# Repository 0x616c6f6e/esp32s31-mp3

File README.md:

# ESP32-S31 MP3 / Q2 风格播放器

当前工程：

- **[V2 裸芯片主板 PCB](hardware-q2-v2/README.md)**：打开 `hardware-q2-v2/q2-v2.kicad_pro`。ESP32-S31NRV16、正面 AM213 BTB、46 × 76 mm 六层板，0201 阻容已改为 0402。当前仅保留电源布线与铺铜，信号待手动布线；几何 DRC、电源未连接及原理图一致性均为 0，174 项信号飞线为有意保留，不能直接投产。[双面预览](hardware-q2-v2/output/pcb-overview.png)。
- [V2 布局及管脚规划依据](hardware-q2-v2-plan/README.md)：保留方案来源；实际已布线管脚以 [V2 当前引脚表](hardware-q2-v2/pin-assignment.md) 为准。

**当前开发外壳为 L 版：适配新的 2.13 英寸 AM213 AMOLED。** 已修改屏幕总成、面壳开孔和固定台，整机仍为50×81.5×15.1 mm。新屏24针BTB不能直接连接已生产主板的21针FPC2，已完成独立双层FPC转接板的3.3 V参考电路和布线；ERC/DRC及原理图一致性检查通过。L版已有完整转接板装配检查副本，仍待FPC工艺审核、实物插合和点亮测试。

- **[最新外壳 L：2.13英寸屏幕适配](mechanical/enclosure-final-l/README.md)**：`Q2_L_AM213_Adapter_Study.FCStd`，直接使用新屏自带触摸盖板，预留17×22 mm转接板空间。[转接板接线规划](hardware-display-adapter/README.md)。

- **[历史外壳 K：旧2.09英寸屏幕](mechanical/enclosure-final-k/README.md)**：`Q2_K_Assembly_Access.FCStd`。已修复J版装入路径与薄壁，但不适用新AM213屏幕；保留作历史参考。

- **[历史外壳 J：后盖胶粘铜螺母版](mechanical/enclosure-final-j/README.md)**：打样复查暂缓，见 [J 版问题记录](mechanical/enclosure-final-j/PREFLIGHT-REVIEW.md)。已由 K 版取代。

- **[历史外壳 I：装配优化版](mechanical/enclosure-final-i/README.md)**：`Q2_I_Serviceable_Assembly.FCStd`。小板采用三颗带限长垫片的螺钉＋侧边限位台，避开 FFC；加厚按键止脱边、增加排线槽与绝缘护边。修正 G/H 版复合实体干涉漏报，使用 I 版完整四件打印包。

- **[历史外壳 H：小板固定加强版](mechanical/enclosure-final-h/README.md)**：`Q2_H_Reinforced_Assembly.FCStd`。加粗四个小板螺柱、加宽根部并增加侧壁加强筋，小板螺钉改为头下长 2 mm 的 M1.6；外形及两板位置沿用 G 版。使用 H 版打印包，G 版保留为历史。

- **[历史外壳 G：薄型树脂装机样件](mechanical/enclosure-final-g/README.md)**：`Q2_G_Thin_Assembly.FCStd`，适配最终主板与 CH32V006 小板，50 × 81.5 × 14.2 mm（含盖板）。CN2/CN3 改为直接焊线装配；修正支柱、马达托座、屏幕排线和按键避让。附四件打印文件。电池成品厚度仍待供方确认，装机约束见说明。

- [最终主板与按键板 FreeCAD 检查](mechanical/final-board-review/README.md)：采用 `hardware-q2/ProPrj_esp32s31-mp4_2026-09-22.kicad_pro` 为最终主板；两板已导入 `Q2_Final_Mainboard_Assembly.FCStd`。四个主板安装孔与原柱对齐，但发现马达/耳机座、C13/屏幕排线干涉，详见检查报告。

- [独立滑环与按键小板 C](hardware-controls/README.md)：打开 `hardware-controls/controls.kicad_pro`；44 × 34 × 0.8 mm，CH32V006F8U6 读取触摸环与四个机械键，通过 I²C 上报，POWER 独立上拉、按下为低；使用 12P / 0.5 mm / 40 mm 异面 FFC。当前整机机械装配见 K 版外壳，需另行完成小板固件及实物触摸标定。
- [已生产的模组版主板](hardware-q2/ProPrj_esp32s31-mp4_2026-09-22.kicad_pro)：当前保存工程为 `ProPrj_esp32s31-mp4_2026-09-22`；原始生产 Gerber 的审查记录见 [打板检查](hardware-q2/gerber-review-20260922/README.md)。
- [H1/H2 端子、马达和电池规划](mechanical/connector-layout/README.md)：当前摆放版使用 JST ACH 两芯/三芯端子，新增 FreeCAD 装配及线束通道检查。
- [历史外壳 F](mechanical/enclosure-q2-f/README.md)：保留早期外观方案；当前装配应参考 L 版。

旧 `hardware/`、`hardware-q2-placement/` 和旧主板导出文件已从当前目录移除，可从 Git 历史查找。根目录的 PDF、嘉立创 `.epro2` / `.epro` 及 Gerber 压缩包是原始资料。

历史摆放版已有主板与外壳适配；用户新布局 `hardware-q2-layout` 已用于最新小板/排线装配，其最终版本的四个主板安装孔已确认与原柱对齐；完整复查以最新报告为准。屏幕 FPC 插接细节、完整器件高度、具体电池型号仍需确认。独立滑环及五键小板见 `hardware-controls/`；两板接口针序已核对，排线插接、小板触摸与摇摆按键仍需实物验证。[排线采购与装配说明](hardware-controls/mechanical/FFC-INTERCONNECT.md)。详细尺寸、检查范围和后续事项见上述工程说明。

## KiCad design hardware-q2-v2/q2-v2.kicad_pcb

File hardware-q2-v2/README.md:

# Q2 V2 裸芯片主板 · 2026-09-24

打开 **q2-v2.kicad_pro**。这是 ESP32-S31NRV16 裸芯片版的独立工程，当前按用户要求改为 **0402 阻容、电源分区铺铜并就近打过孔，信号待手动布线**。不是可打板文件。原生产主板 `hardware-q2` 的 PCB 保持原文件哈希。

此前将 21 个电容、10 个电阻及 L105（实际为 0Ω 电阻）从英制 0201 改为 0402（公制 1005）；L101–L104 的射频/滤波电感不在阻容替换范围内。随后检查发现原嘉立创导入的 0402 与 KiCad 标准焊盘混用，现已统一全部 62 个电阻类封装（含 L105）及 72 个电容封装，原理图、符号库、PCB 和 3D 模型同步使用下面两套项目内标准封装。密集区已调整间距，接口和安装孔位置保持不变。

| 类型 | 项目封装 | 焊盘尺寸 | 两焊盘中心距 |
|---|---|---|---|
| 0402 电阻 | `V2:R_0402_1005Metric` | 0.54 × 0.64 mm，圆角矩形 | 1.02 mm |
| 0402 电容 | `V2:C_0402_1005Metric` | 0.56 × 0.62 mm，圆角矩形 | 0.96 mm |

两者来自 KiCad 10 标准库，阻焊/锡膏使用标准继承设置。原有 0603/0805 电容和 1206 电流采样电阻保留原尺寸；过时的 134 个按位号命名的 0402 封装已移除，避免误用。`0402-standardization.json` 记录原始尺寸、统一后尺寸、位置及检查结果；运行 `scripts/audit_0402.py` 可核对所有实例的焊盘、阻焊/锡膏、模型及原理图关联。

删除了 2,090 段信号走线、155 个信号过孔；另重建主控局部电源引出。保留供电、GND/GBAT、稳压器开关/反馈/自举、电荷泵及马达负载回路。电源使能、温度采样、通信、时钟、射频、音频输出等信号均需后续手动布线。精确网络允许列表和改封装清单见 `power-only-0402.json`。

## 工程内容

- `q2-v2.kicad_pcb`：46 × 76 mm，6 层，名义板厚 1.6 mm；198 个器件，双面装配，普通通孔。
- `q2-v2.kicad_sch`：根页及 19 个功能子页，与 PCB 的器件实例和编号焊盘关联。
- `V2.kicad_sym`、`V2.pretty`、`models3d`：项目局部符号、封装和模型。常规 R/C/L 使用 KiCad 标准模型，需安装 KiCad 10 的 3D 模型库。
- `pin-assignment.md`、`q2_v2_pins.h`：从实际 PCB 生成的管脚表和 GPIO 宏；不是已验证的 BSP。
- `output/drc.json`、`erc.json`、`netlist-consistency.json`、`validation-summary.json`：最终检查记录。
- `output/q2-v2-assembly.step`、`case-fit.json`：主板装配模型及相对 L 版外壳的名义干涉检查。
- `output/front-review.svg/png`、`back-review.svg/png`：布局预览；`output/assembly-front.svg`、`assembly-back.svg` 为装配图。
- `output/power-map.svg/png`：In2/In3 实际填充后的电源铜区，按网络着色，均为顶视坐标；`power-pours.json` 记录铜区面积及电源连通性检查。
- 本地 `output/archive` 和路由会话为未提交的中间候选；Git 保留最终报告、模型与建板基线。`scripts` 中的建板及试布线脚本是过程记录，部分依赖本地路由运行时。**不要重新运行 build_v2、prepare_routing、route_usb_and_export 等初始化脚本覆盖当前成品布线。**

## 实现的电路与布局

主控改为 ESP32-S31NRV16，采用乐鑫官方 WROOM-3 V1.2 参考设计的裸芯片电源、40 MHz 晶振、PSRAM 供电和射频匹配起始网络，外接 W25Q128JVSIQ 16 MB 启动 Flash。天线暂定 U.FL/IPEX 外接柔性天线，尚未选定最终天线及安装位置。

屏幕采用正面 OK-23GF024-04，JDISP1 中心以板框左上原点计 `(30.0, 29.2) mm`，旋转 90°。板框原点对应 KiCad 坐标 `(128.868, 67.647) mm`。主控、存储和射频在上部，音频在左下，充电、USB 和电池接口在下部；新增低速电路主要放在背面。

为保持已完成 CH32 按键板的 POWER 上拉行为，新增常供电 3.3 V、跨断电电源域的信号隔离和关机脉冲电路。FPC1 的 2 脚改由常供电 3.3 V 供电；系统 I²C 使用 GPIO6/7 的 **LP I²C**，不能当成第三个普通 HP I²C 控制器初始化。UART 自动下载采用交叉晶体管电路；GPIO60/61 为启动配置，GPIO0 用于按键检测。

已修正 V1 中 CS43131 的 SCL/SDA 对应关系：物理 1 脚 SCL、39 脚 SDA。USB 屏蔽固定焊盘接地，USB 定位孔按厂家图改为 Ø0.55 mm NPTH。保留原外部接口和安装孔锚点。

| 焊线接口 | 焊盘 | 网络 | 用途 |
|---|---|---|---|
| CN2 | 1 | VBAT | 电池正极 |
| CN2 | 2 | BAT_TS | 电池温度检测，不可当作负极 |
| CN2 | 3 | GBAT | 电池负极，保留电量计采样回路，不要任意短接到其它 GND 点 |
| CN3 | 1 / 2 | MOTOR_OUT_P / MOTOR_OUT_N | 马达两端，均不是直接接地端 |

## 校验结果及边界

当前原生 KiCad 10 检查：**几何 DRC 违规 0 项、原理图一致性 0 项、电源未连接 0 项；信号未连接 174 项，符合本次保留飞线的要求**。原理图电路未改变，既有 ERC 为 0 项；另重新逐项比对 198 个器件、704 个编号焊盘的 XML 网表与 PCB，网络不一致为 0。所有阻容均已无 0201 封装，信号走线/过孔残留为 0。

DRC 使用工程内设置：最小线宽/间距 0.10/0.10 mm，保留少量 Ø0.35/0.15 mm 通孔，常规过孔 Ø0.45/0.20 mm；两层连续 GND 加外层铺地及就近地过孔。DRC 和铜区连通性检查不能替代电流/温升验证。

### 电源铺铜与过孔

本次不移动器件或更改原理图网络。In2.Cu（PWR）以 VCC_3V3 为主，In3.Cu（工程名称 SINGAL）放置其余局部电源铜区，必要的跨区连接借用少量 In2 区域。包括 GBAT 在内共 12 个供电/回流分区，彼此保持网络隔离；In1/In4 继续作为整面公共 GND。后续布信号需避开这些电源铜区，或重新填铜并复查电源连通性。

删除直流供电网络的内层分配走线，改为实际连通的铺铜；焊盘附近采用 Ø0.45/0.20 mm、双面盖油的过孔连接内层。普通电源孔避开 SMD 焊盘，保留必要的短表层引出，单段最长 2.0 mm；充电器和降压的大电流节点补充并联过孔。开关节点、反馈、自举、电荷泵以及马达负载回路仍保留必要短线，不能直接视为直流电源平面。主控原有 GND 散热焊盘通孔保留。

`scripts/audit_power_pours.py` 核对电源及地无未连接、直流内层分配线为零、信号铜残留为零，并输出实际填充铜区图。`build_power_pours.py` 和 `bridge_power_pours.py` 是生成过程脚本，依赖本地未提交的 `output/power-pour-spines.kicad_pcb`；不要作为日常更新命令重复执行。后续直接在 KiCad 编辑当前 PCB 并按 B 重新填铜。旧的 `output/power-width-*.json`、`retained-routing.json` 为改铺铜前的历史检查，本版以 `power-pours.json` 和 `validation-summary.json` 为准。

`drc.json` 明列 5 类未启用检查，包括缺少 courtyard、线端未居中过孔等，不能把 0 项理解为完整 DFM 认证。导入封装没有统一的装配 courtyard；已用名义 3D 模型补充器件碰撞检查，但没有验证供应商公差或装配工具空间。

FreeCAD 检查未发现器件模型之间的实体重叠，亦未发现主板组件与所选 L 版外壳、后盖、电池及马达占位的硬碰撞。仅 FPC1 与按键排线插入包络重叠约 1.071 mm³，属于预期插接区域。螺钉孔、测试点、CN2/CN3 焊线焊盘没有实体器件模型；新增晶振和主控模型为名义外形。该结果不等同于屏幕尾排线可插入、插拔路径和尺寸公差已验证。

## 打板前尚待完成的签核

1. **完成所有信号布线。** 包括电源使能、温度采样、USB、Flash、屏幕、音频、射频和晶振。USB 旧版线长结果已失效；`output/usb-routing.json` 是改版前的历史记录，不代表当前 PCB。下单前选定厂家叠层，计算线宽、间距、参考面并复核全链路差分耦合与偏斜；目前没有受控阻抗签核。
2. **射频与晶振。** 匹配值来自官方模块参考，但参考模块叠层不同，不能直接等同于本板的 50 Ω。本次匹配/负载电容及 0Ω 链路放大为 0402，寄生参数变化，原值仅保留为调试起点；需重布短线并实测匹配和晶振。40 MHz 晶振需匹配负载、精度及封装，不能只按频率采购。
3. **AM213 屏幕。** 按此前用户决定继续使用 3.3 V；项目内已保存的 [OSPTEK 官方参考原理图](../hardware-display-adapter/reference/osptek-official/PCB-2.13&1.96AMOLED-qspi转接板.pdf) 将 AM213 的 11/12/15/16 脚接到 VCC3V3，因此有原厂参考电路依据。该接法与早期规格书 PMIC 最低 3.4 V 的文字仍有差异，需实测启动、最大亮度、电源余量和温度边界，不能当作所有屏幕批次的保证。BTB 朝向、尾排线实际折弯与够长需用实物确认，不能仅靠 nominal STEP 认定可插接。
4. **供电和装配工艺。** 裸芯片 EP 内含 25 个散热通孔，需向板厂确认树脂填孔、电镀盖孔/平整焊盘工艺，避免焊料流失；0.15 mm 小孔、细线距及双面装配须与所选订单工艺一致。验证充电/峰值电流、主电源掉电、AON 反灌隔离及关机脉冲时序；尚未做上电、固件、信号完整性、热或 EMC 测试。

因此本目录交付的是**供手动完成信号布线的 PCB 工程**，没有导出标为可生产的 Gerber 包。

## 音频接地与后续布线

本板建议保留连续的公共 GND 平面，通过器件分区和回流路径隔离噪声，不另建孤立 AGND 铜岛或在 I²S 回流下开地缝。充电、降压与马达的大电流回路应局部闭合并远离 DAC/耳机回路；音频电源的滤波与去耦独立考虑。GBAT 是电量计采样回路，不是音频地，不可直接并到其它地焊盘。

**HPREFA/HPREFB 是例外的参考回路要求，不等于整块音频分地。** CS43131 手册第 8.3 节要求 U2 的 13、17 脚分别独立走线到耳机座参考地，再在耳机座地处通过过孔接系统地。目前这两脚仍归属公共 GND，现有铺铜会直接接入，尚未实现 Kelvin 回路。手动布线时应使用独立参考地网络与耳机座处的 net-tie（或局部禁布铜并严格控制公共网拓扑）实现，不能将当前公共地填充视为该要求已满足。GNDA/GNDD/GNDCP 和散热焊盘则继续采用低阻抗接地。依据：[CS43131 数据手册第 8.1–8.4 节](https://statics.cirrus.com/pubs/proDatasheet/CS43131_DS1155F2.pdf#page=140)。

## 参考依据

- [乐鑫 ESP32-S31 硬件设计指南](https://docs.espressif.com/projects/esp-hardware-design-guidelines/en/latest/esp32s31/schematic-checklist.html)，以及项目内 `esp32-s31_datasheet_en.pdf` v0.5；官方模块参考工程保存在 `reference/s31-module`。
- [CS43131 官方手册](https://statics.cirrus.com/pubs/proDatasheet/CS43131_DS1155F2.pdf)。
- [嘉立创 PCB 制程能力](https://jlcpcb.com/capabilities/pcb-capabilities)与[受控阻抗叠层](https://jlcpcb.com/impedance)。生产叠层和工艺应以实际订单确认为准。

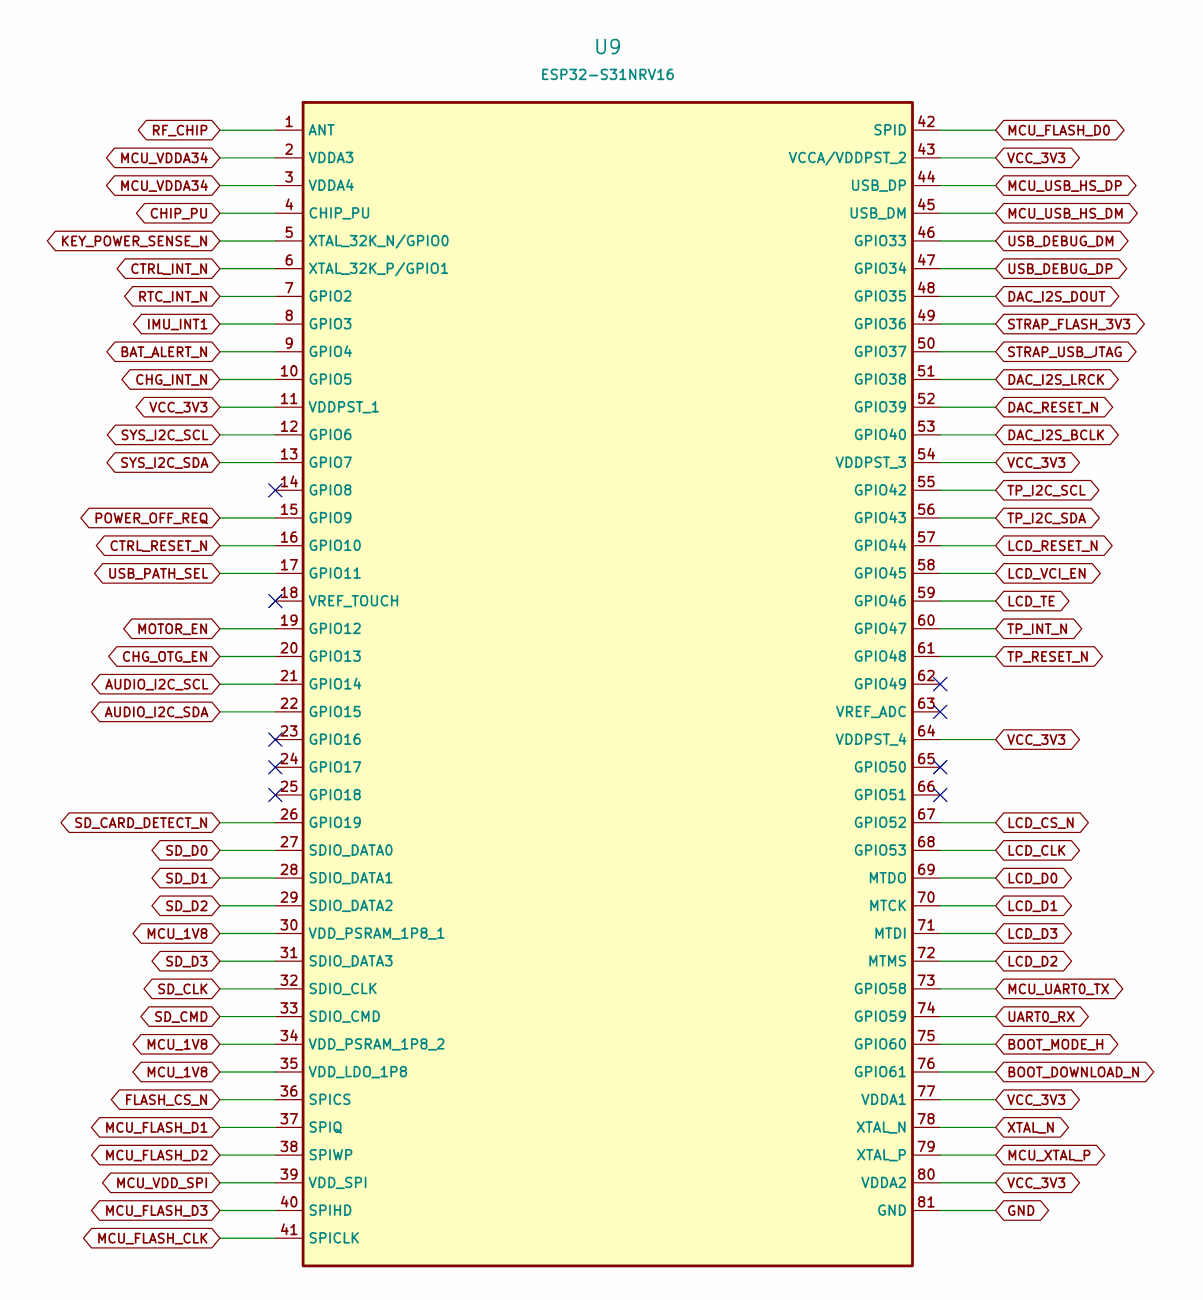
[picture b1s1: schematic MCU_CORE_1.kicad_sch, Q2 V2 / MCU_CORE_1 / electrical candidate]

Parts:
U9: ESP32-S31NRV16; FP_U9

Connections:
AUDIO_I2C_SCL: U9.21 (GPIO14); also elsewhere on the board
AUDIO_I2C_SDA: U9.22 (GPIO15); also elsewhere on the board
BAT_ALERT_N: U9.9 (GPIO4); also elsewhere on the board
BOOT_DOWNLOAD_N: U9.76 (GPIO61); also elsewhere on the board
BOOT_MODE_H: U9.75 (GPIO60); also elsewhere on the board
CHG_INT_N: U9.10 (GPIO5); also elsewhere on the board
CHG_OTG_EN: U9.20 (GPIO13); also elsewhere on the board
CHIP_PU: U9.4 (CHIP_PU); also elsewhere on the board
CTRL_INT_N: U9.6 (XTAL_32K_P/GPIO1); also elsewhere on the board
CTRL_RESET_N: U9.16 (GPIO10); also elsewhere on the board
DAC_I2S_BCLK: U9.53 (GPIO40); also elsewhere on the board
DAC_I2S_DOUT: U9.48 (GPIO35); also elsewhere on the board
DAC_I2S_LRCK: U9.51 (GPIO38); also elsewhere on the board
DAC_RESET_N: U9.52 (GPIO39); also elsewhere on the board
FLASH_CS_N: U9.36 (SPICS); also elsewhere on the board
GND: U9.81 (GND); also elsewhere on the board
IMU_INT1: U9.8 (GPIO3); also elsewhere on the board
KEY_POWER_SENSE_N: U9.5 (XTAL_32K_N/GPIO0); also elsewhere on the board
LCD_CLK: U9.68 (GPIO53); also elsewhere on the board
LCD_CS_N: U9.67 (GPIO52); also elsewhere on the board
LCD_D0: U9.69 (MTDO); also elsewhere on the board
LCD_D1: U9.70 (MTCK); also elsewhere on the board
LCD_D2: U9.72 (MTMS); also elsewhere on the board
LCD_D3: U9.71 (MTDI); also elsewhere on the board
LCD_RESET_N: U9.57 (GPIO44); also elsewhere on the board
LCD_TE: U9.59 (GPIO46); also elsewhere on the board
LCD_VCI_EN: U9.58 (GPIO45); also elsewhere on the board
MCU_1V8: U9.30 (VDD_PSRAM_1P8_1), U9.34 (VDD_PSRAM_1P8_2), U9.35 (VDD_LDO_1P8); also elsewhere on the board
MCU_FLASH_CLK: U9.41 (SPICLK); also elsewhere on the board
MCU_FLASH_D0: U9.42 (SPID); also elsewhere on the board
MCU_FLASH_D1: U9.37 (SPIQ); also elsewhere on the board
MCU_FLASH_D2: U9.38 (SPIWP); also elsewhere on the board
MCU_FLASH_D3: U9.40 (SPIHD); also elsewhere on the board
MCU_UART0_TX: U9.73 (GPIO58); also elsewhere on the board
MCU_USB_HS_DM: U9.45 (USB_DM); also elsewhere on the board
MCU_USB_HS_DP: U9.44 (USB_DP); also elsewhere on the board
MCU_VDDA34: U9.2 (VDDA3), U9.3 (VDDA4); also elsewhere on the board
MCU_VDD_SPI: U9.39 (VDD_SPI); also elsewhere on the board
MCU_XTAL_P: U9.79 (XTAL_P); also elsewhere on the board
MOTOR_EN: U9.19 (GPIO12); also elsewhere on the board
POWER_OFF_REQ: U9.15 (GPIO9); also elsewhere on the board
RF_CHIP: U9.1 (ANT); also elsewhere on the board
RTC_INT_N: U9.7 (GPIO2); also elsewhere on the board
SD_CARD_DETECT_N: U9.26 (GPIO19); also elsewhere on the board
SD_CLK: U9.32 (SDIO_CLK); also elsewhere on the board
SD_CMD: U9.33 (SDIO_CMD); also elsewhere on the board
SD_D0: U9.27 (SDIO_DATA0); also elsewhere on the board
SD_D1: U9.28 (SDIO_DATA1); also elsewhere on the board
SD_D2: U9.29 (SDIO_DATA2); also elsewhere on the board
SD_D3: U9.31 (SDIO_DATA3); also elsewhere on the board
STRAP_FLASH_3V3: U9.49 (GPIO36); also elsewhere on the board
STRAP_USB_JTAG: U9.50 (GPIO37); also elsewhere on the board
SYS_I2C_SCL: U9.12 (GPIO6); also elsewhere on the board
SYS_I2C_SDA: U9.13 (GPIO7); also elsewhere on the board
TP_I2C_SCL: U9.55 (GPIO42); also elsewhere on the board
TP_I2C_SDA: U9.56 (GPIO43); also elsewhere on the board
TP_INT_N: U9.60 (GPIO47); also elsewhere on the board
TP_RESET_N: U9.61 (GPIO48); also elsewhere on the board
UART0_RX: U9.74 (GPIO59); also elsewhere on the board
USB_DEBUG_DM: U9.46 (GPIO33); also elsewhere on the board
USB_DEBUG_DP: U9.47 (GPIO34); also elsewhere on the board
USB_PATH_SEL: U9.17 (GPIO11); also elsewhere on the board
VCC_3V3: U9.11 (VDDPST_1), U9.43 (VCCA/VDDPST_2), U9.54 (VDDPST_3), U9.64 (VDDPST_4), U9.77 (VDDA1), U9.80 (VDDA2); also elsewhere on the board
XTAL_N: U9.78 (XTAL_N); also elsewhere on the board

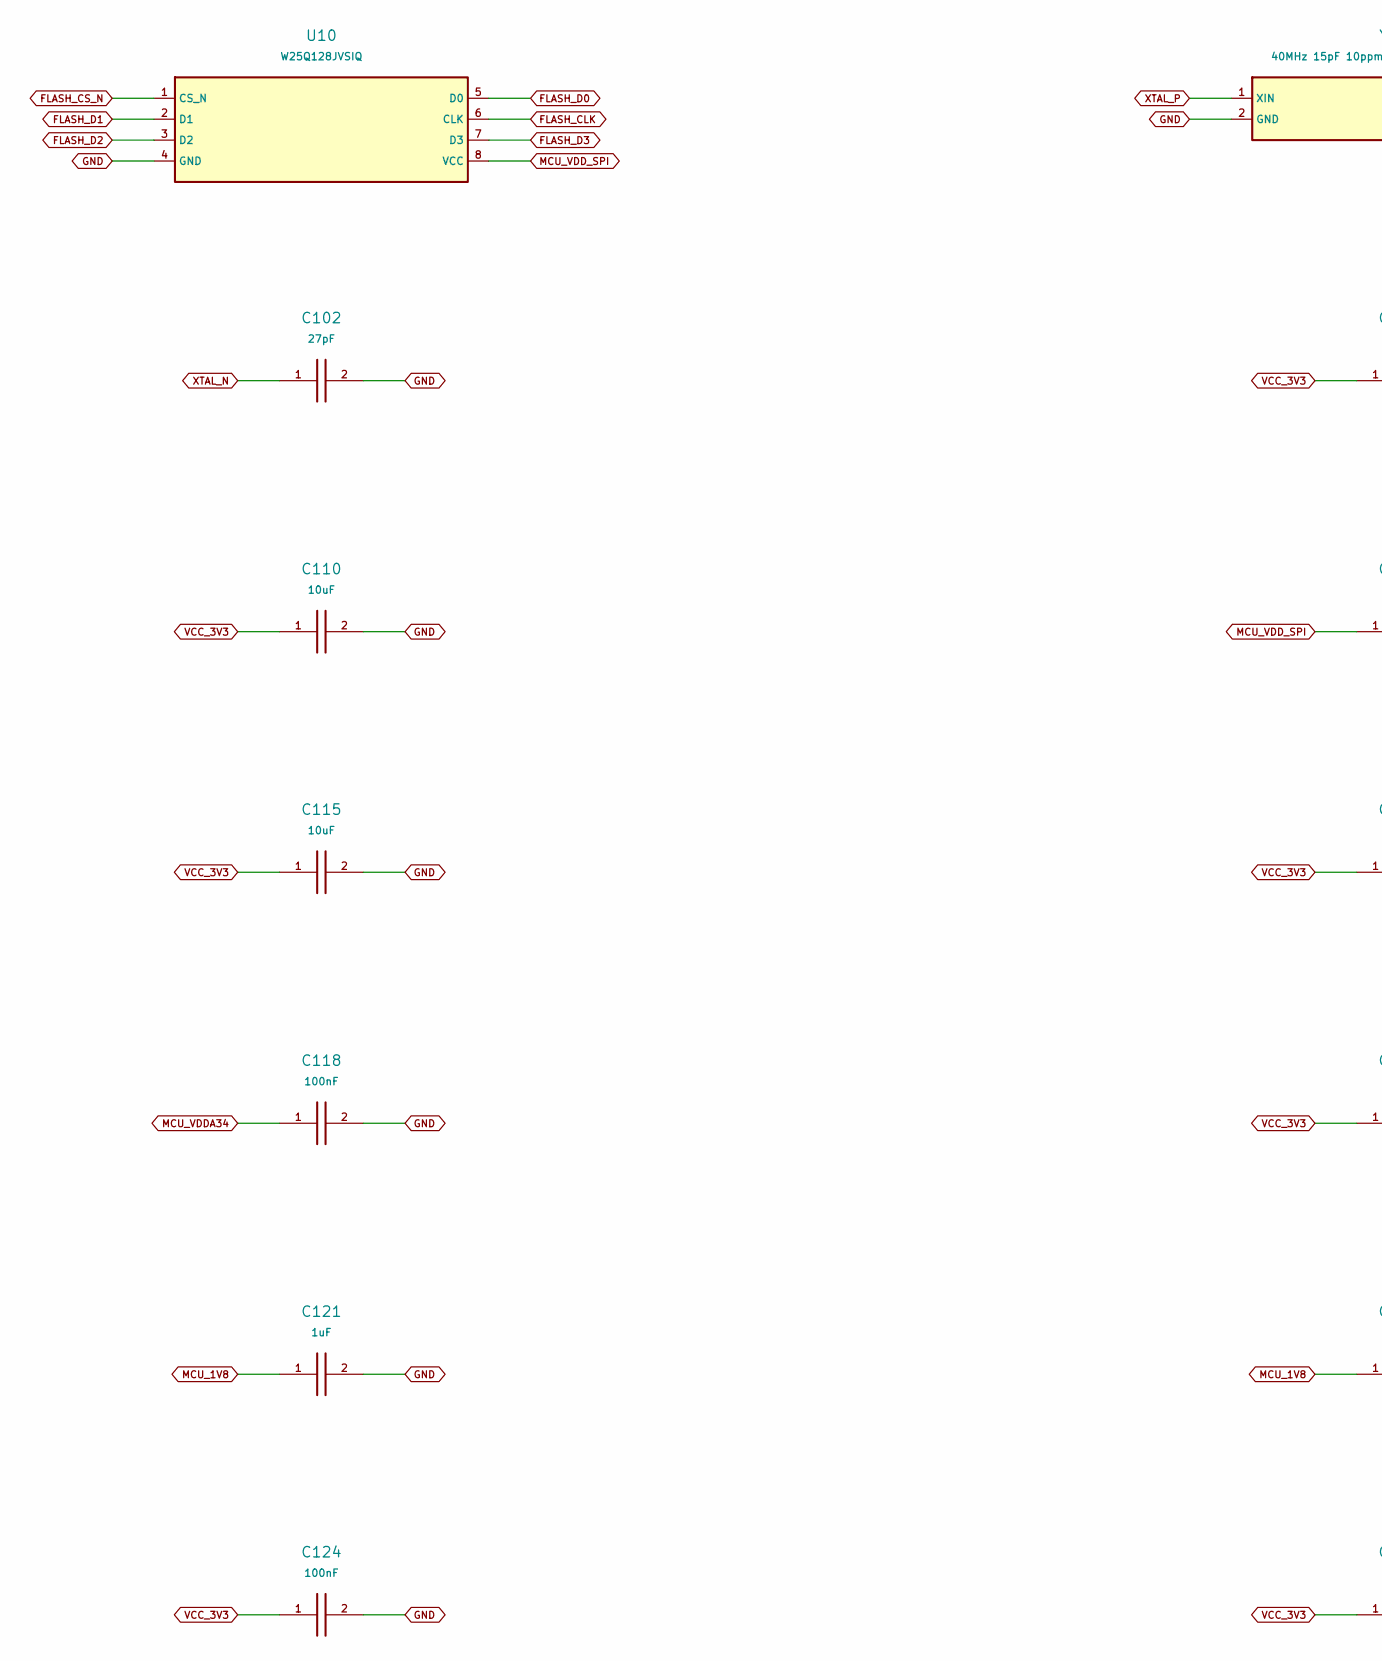
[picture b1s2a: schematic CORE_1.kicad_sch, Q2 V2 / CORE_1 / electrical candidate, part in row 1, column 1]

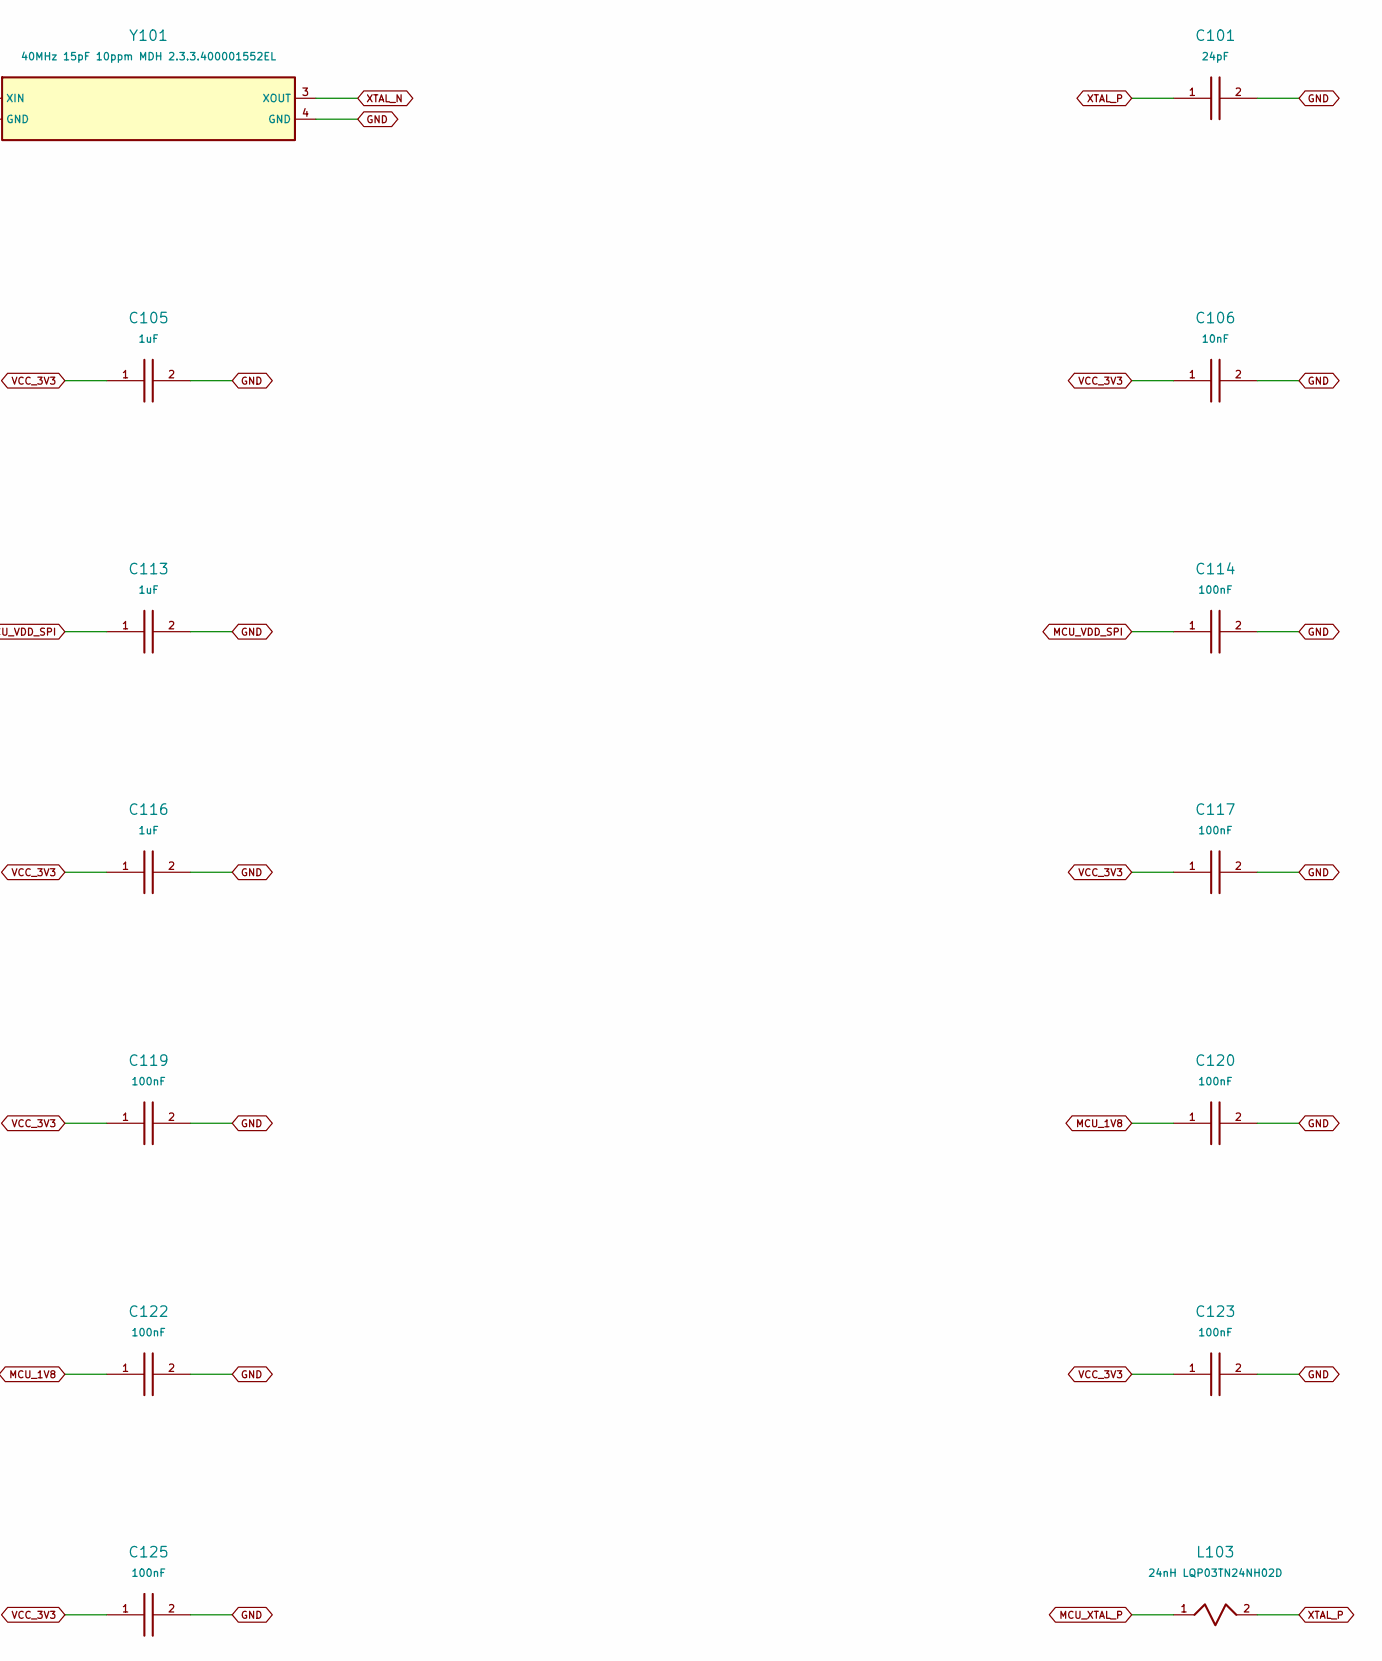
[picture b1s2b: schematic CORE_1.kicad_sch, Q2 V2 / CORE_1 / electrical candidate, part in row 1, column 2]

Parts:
C101: 24pF; C_0402_1005Metric
C102: 27pF; C_0402_1005Metric
C105, C113, C116, C121: 1uF; C_0402_1005Metric
C106: 10nF; C_0402_1005Metric
C110, C115: 10uF; C_0402_1005Metric
C114, C117, C118, C119, C120, C122, C123, C124, C125: 100nF; C_0402_1005Metric
L103: 24nH LQP03TN24NH02D; FP_L103
U10: W25Q128JVSIQ; FP_U10
Y101: 40MHz 15pF 10ppm MDH 2.3.3.400001552EL; FP_Y101

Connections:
FLASH_CLK: U10.6 (CLK); also elsewhere on the board
FLASH_CS_N: U10.1 (CS_N); also elsewhere on the board
FLASH_D0: U10.5 (D0); also elsewhere on the board
FLASH_D1: U10.2 (D1); also elsewhere on the board
FLASH_D2: U10.3 (D2); also elsewhere on the board
FLASH_D3: U10.7 (D3); also elsewhere on the board
GND: C101.2, C102.2, C105.2, C106.2, C110.2, C113.2, C114.2, C115.2, C116.2, C117.2, C118.2, C119.2, C120.2, C121.2, C122.2, C123.2, C124.2, C125.2, U10.4 (GND), Y101.2 (GND), Y101.4 (GND); also elsewhere on the board
MCU_1V8: C120.1, C121.1, C122.1; also elsewhere on the board
MCU_VDDA34: C118.1; also elsewhere on the board
MCU_VDD_SPI: C113.1, C114.1, U10.8 (VCC); also elsewhere on the board
MCU_XTAL_P: L103.1; also elsewhere on the board
VCC_3V3: C105.1, C106.1, C110.1, C115.1, C116.1, C117.1, C119.1, C123.1, C124.1, C125.1; also elsewhere on the board
XTAL_N: C102.1, Y101.3 (XOUT); also elsewhere on the board
XTAL_P: C101.1, L103.2, Y101.1 (XIN)

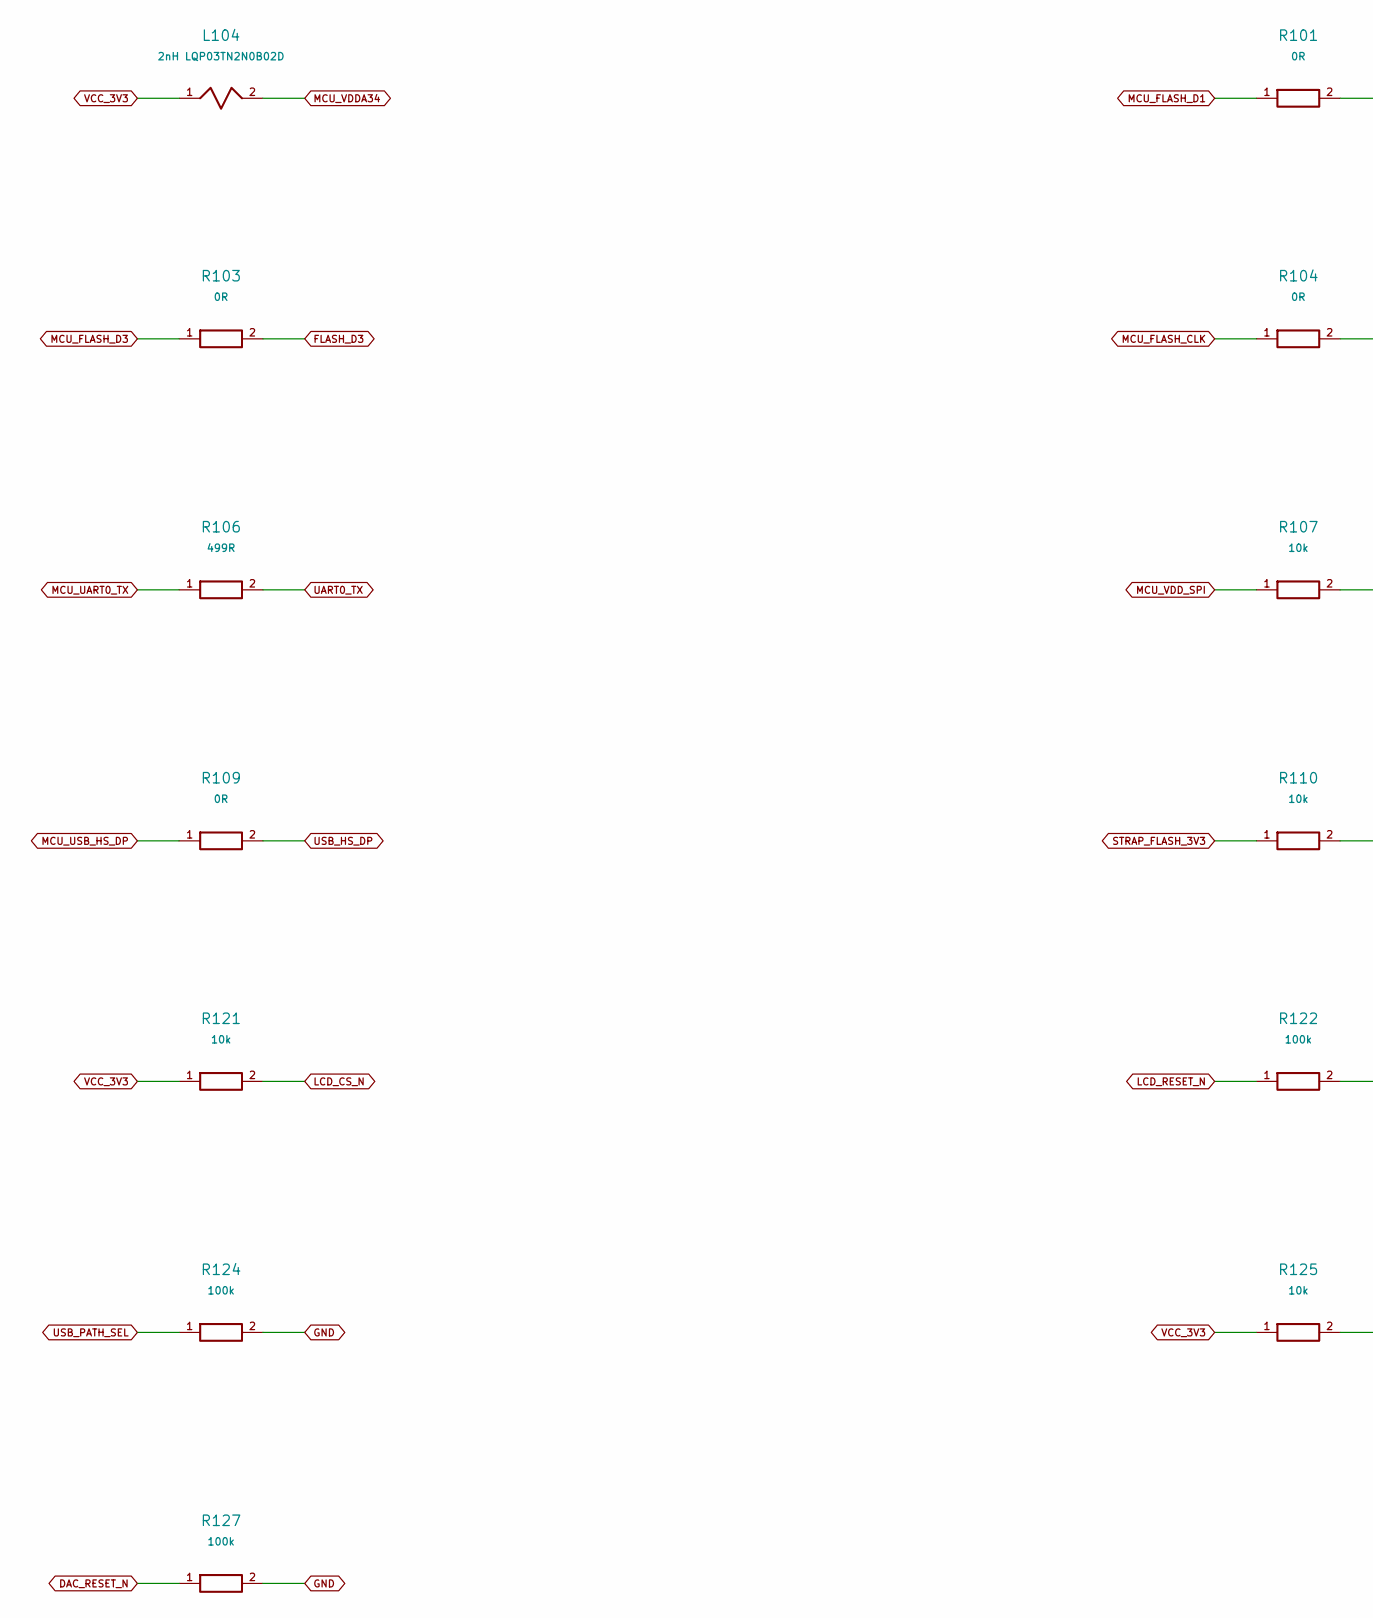
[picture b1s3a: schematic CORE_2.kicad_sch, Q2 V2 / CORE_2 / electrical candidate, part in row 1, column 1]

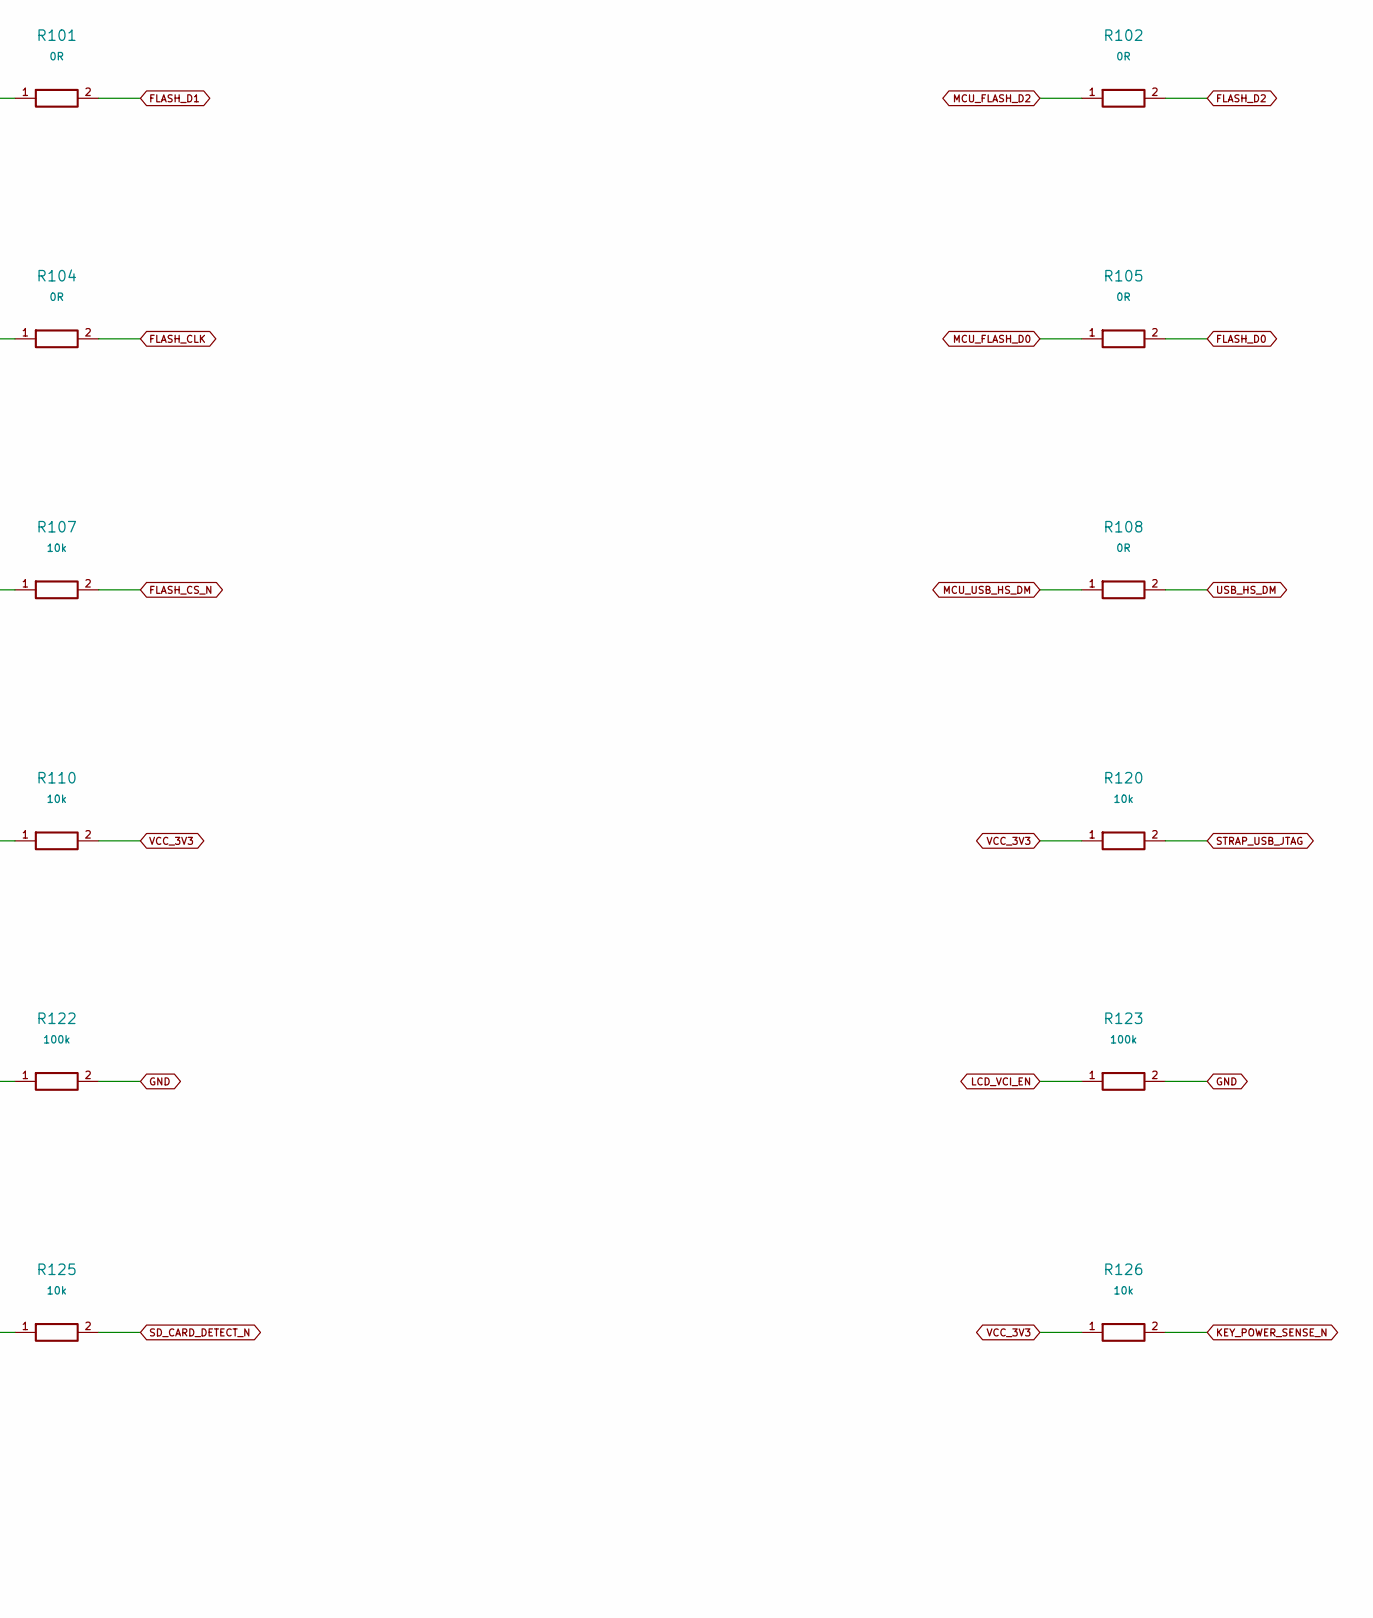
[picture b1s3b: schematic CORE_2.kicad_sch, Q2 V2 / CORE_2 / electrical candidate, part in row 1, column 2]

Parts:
L104: 2nH LQP03TN2N0B02D; FP_L104
R101, R102, R103, R104, R105, R108, R109: 0R; R_0402_1005Metric
R106: 499R; R_0402_1005Metric
R107, R110, R120, R121, R125, R126: 10k; R_0402_1005Metric
R122, R123, R124, R127: 100k; R_0402_1005Metric

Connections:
DAC_RESET_N: R127.1; also elsewhere on the board
FLASH_CLK: R104.2; also elsewhere on the board
FLASH_CS_N: R107.2; also elsewhere on the board
FLASH_D0: R105.2; also elsewhere on the board
FLASH_D1: R101.2; also elsewhere on the board
FLASH_D2: R102.2; also elsewhere on the board
FLASH_D3: R103.2; also elsewhere on the board
GND: R122.2, R123.2, R124.2, R127.2; also elsewhere on the board
KEY_POWER_SENSE_N: R126.2; also elsewhere on the board
LCD_CS_N: R121.2; also elsewhere on the board
LCD_RESET_N: R122.1; also elsewhere on the board
LCD_VCI_EN: R123.1; also elsewhere on the board
MCU_FLASH_CLK: R104.1; also elsewhere on the board
MCU_FLASH_D0: R105.1; also elsewhere on the board
MCU_FLASH_D1: R101.1; also elsewhere on the board
MCU_FLASH_D2: R102.1; also elsewhere on the board
MCU_FLASH_D3: R103.1; also elsewhere on the board
MCU_UART0_TX: R106.1; also elsewhere on the board
MCU_USB_HS_DM: R108.1; also elsewhere on the board
MCU_USB_HS_DP: R109.1; also elsewhere on the board
MCU_VDDA34: L104.2; also elsewhere on the board
MCU_VDD_SPI: R107.1; also elsewhere on the board
SD_CARD_DETECT_N: R125.2; also elsewhere on the board
STRAP_FLASH_3V3: R110.1; also elsewhere on the board
STRAP_USB_JTAG: R120.2; also elsewhere on the board
UART0_TX: R106.2; also elsewhere on the board
USB_HS_DM: R108.2; also elsewhere on the board
USB_HS_DP: R109.2; also elsewhere on the board
USB_PATH_SEL: R124.1; also elsewhere on the board
VCC_3V3: L104.1, R110.2, R120.1, R121.1, R125.1, R126.1; also elsewhere on the board

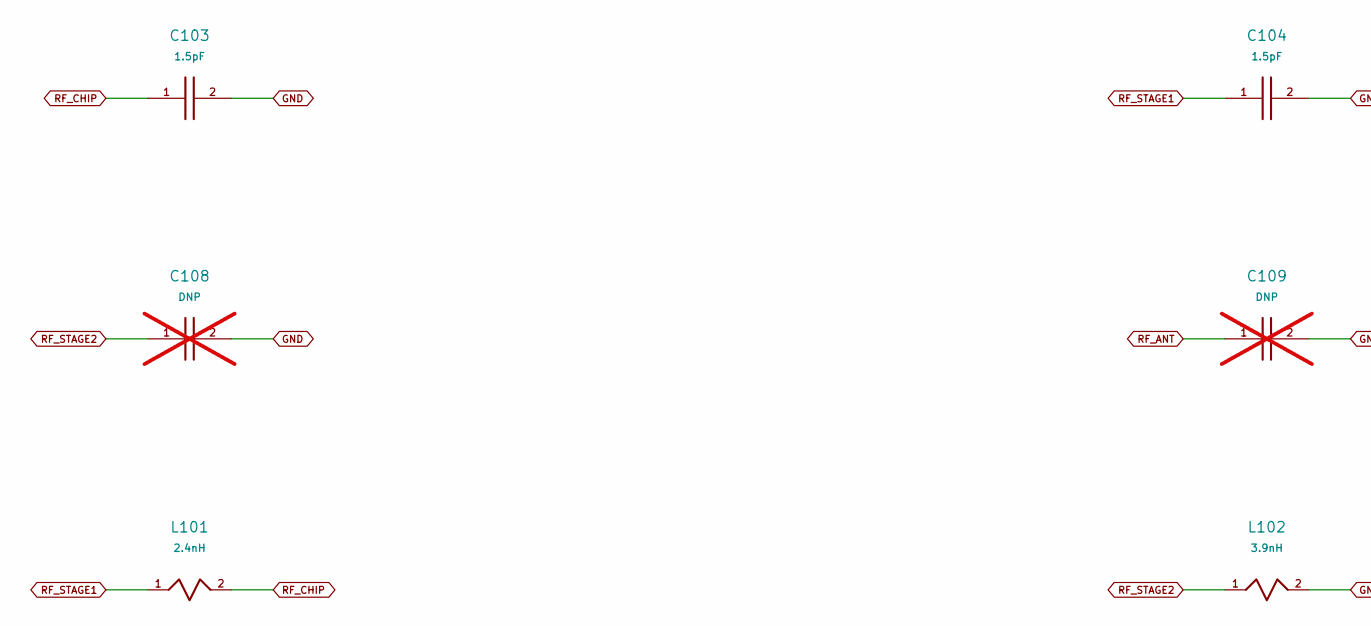
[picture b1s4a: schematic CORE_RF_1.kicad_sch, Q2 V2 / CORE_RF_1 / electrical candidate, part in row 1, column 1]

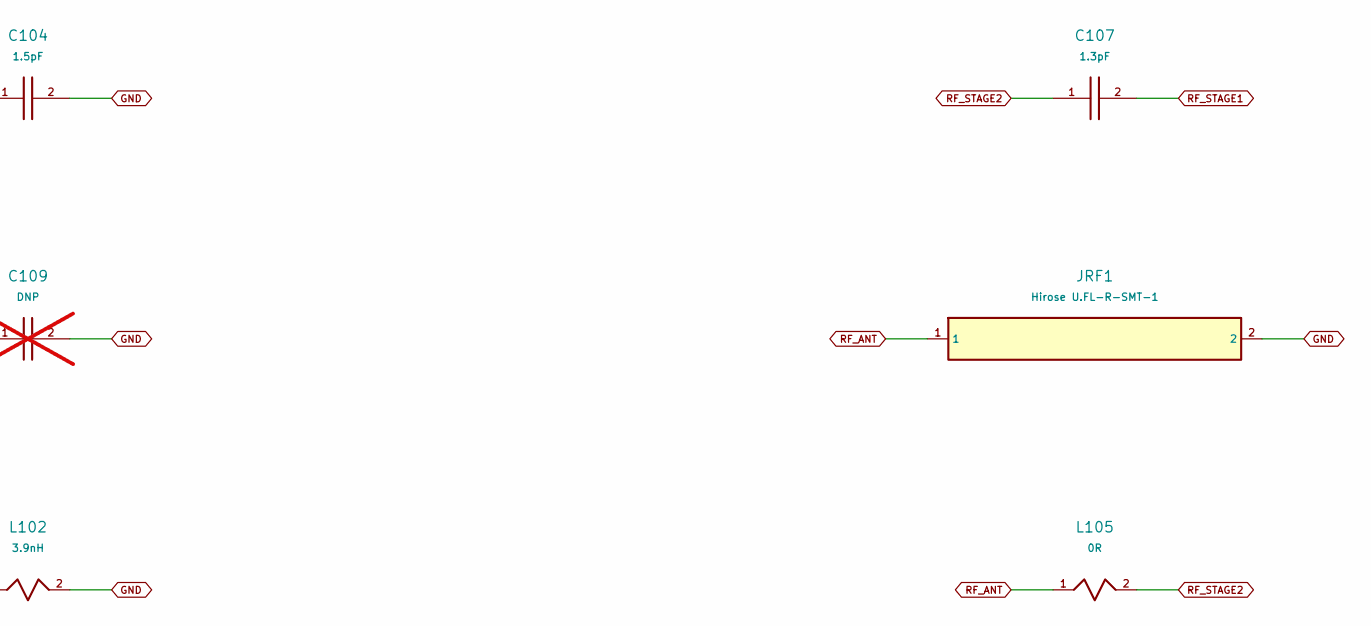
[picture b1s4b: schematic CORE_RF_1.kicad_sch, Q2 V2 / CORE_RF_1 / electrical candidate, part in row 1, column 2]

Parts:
C103, C104: 1.5pF; C_0402_1005Metric
C107: 1.3pF; C_0402_1005Metric
C108, C109: DNP; C_0402_1005Metric; not fitted
JRF1: Hirose U.FL-R-SMT-1; FP_JRF1
L101: 2.4nH; FP_L101
L102: 3.9nH; FP_L102
L105: 0R; R_0402_1005Metric

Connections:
GND: C103.2, C104.2, C108.2, C109.2, JRF1.2, L102.2; also elsewhere on the board
RF_ANT: C109.1, JRF1.1, L105.1
RF_CHIP: C103.1, L101.2; also elsewhere on the board
RF_STAGE1: C104.1, C107.2, L101.1
RF_STAGE2: C107.1, C108.1, L102.1, L105.2
